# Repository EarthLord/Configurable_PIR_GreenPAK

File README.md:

# Project _PIR<sup>PAK</sup>_

### Objective

Create a PIR (Passive InfraRed) sensor system to detect movement using low cost AnalogPAK IC from Renesas (SLG47001). PIR sensors detect motion of heat, thus are used in security systems, building automation and wildlife conservation industries extensively. The sensitivity of sensing of movement is configurable by users using an `UP` and `DOWN` button.

### SLG47001 design 

### Schematic

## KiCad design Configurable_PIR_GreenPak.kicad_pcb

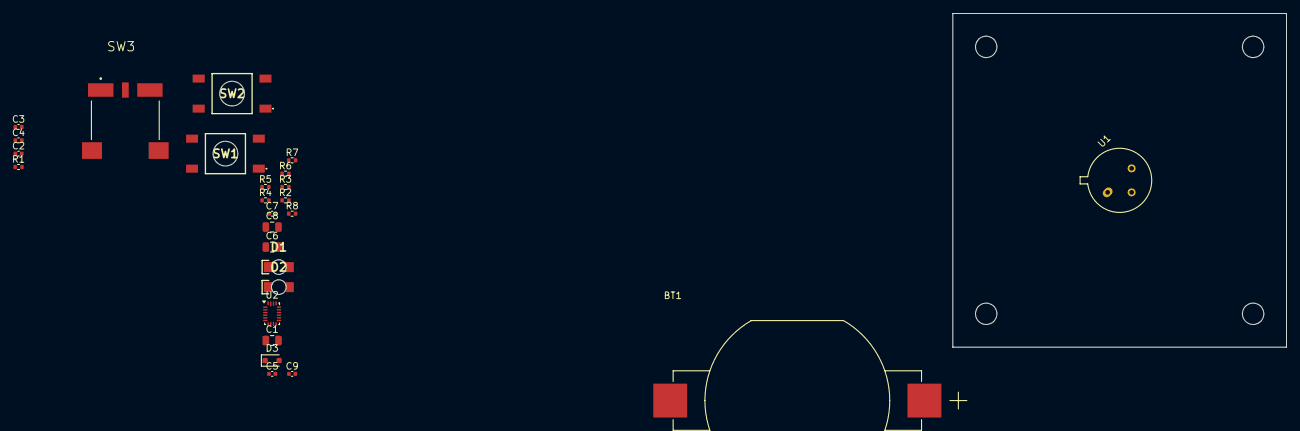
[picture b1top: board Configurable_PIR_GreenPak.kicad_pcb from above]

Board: 4 copper layers, 50.0 x 50.0 mm, 30 parts (0 on the bottom side), 18 nets, no tracks yet.

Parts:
BT1: Battery_Cell; MPD_BU2477SM-JJ-GTR
C1, C6, C8: 22u; C_0805_2012Metric
C2: 1n; C_0402_1005Metric
C3, C4, C5: 100n; C_0402_1005Metric
C7, C9: 6n8; C_0402_1005Metric
D1: Red LED; 5990Kxx_reverse_LED
D2: Green LED; 5990Kxx_reverse_LED
D3: CUS10S30,H3F; D_SOD-323
H1, H2, H3, H4: MountingHole; MountingHole_3.2mm_M3
R1, R4: 47k; R_0402_1005Metric
R2, R3: 510E; R_0402_1005Metric
R5, R6, R7, R8: 1M5; R_0402_1005Metric
SW1, SW2: SW_Push; RT3301AF100Q
SW3: SW_SPDT; SW_500ASSP1SM6QE
U1: PIR; TO-5-3
U2: SLG47001V; Renesas_UQFN-20_2x3mm_P0.4mm_LayoutBorder4x6y

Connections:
/DOWN_BTN: SW2.2, U2.15 (GPIO0)
/ENABLE_SW: SW3.2 (B), U2.1 (GPI0)
/LOW_BAT_LED: D1.1 (K), U2.19 (SDA/GPIO5)
/PIR_LED: D2.1 (K), U2.18 (SCL/GPIO4)
/PIR_OUT: C2.1, R1.1, U1.2 (OUT), U2.6 (OA0+)
/STAGE1_OUT: C7.2, C8.1, D3.2 (A), R5.2, U2.8 (OA0_OUT)
/STAGE2_OUT: C9.2, R6.2, U2.9 (OA1_OUT)
/UP_BTN: SW1.2, U2.16 (GPIO1)
/VBAT: BT1.P (+), C1.1, C3.1, C4.1, C5.1, R2.2, R3.2, R7.2, U1.1 (VDD), U2.2 (VDD), U2.14 (VDDA)
/VDD/2_REF: R7.1, R8.2, U2.11 (OA1+)
GND: BT1.N, C1.2, C2.2, C3.2, C4.2, C5.2, C6.2, R1.2, R8.1, SW1.1, SW2.1, SW3.3 (C), U1.3 (GND), U2.3 (GND)
unnamed: C6.1, R4.1
unnamed: D1.2 (A), R2.1
unnamed: D2.2 (A), R3.1
unnamed: C7.1, D3.1 (K), R4.2, R5.1, U2.7 (OA0-)
unnamed: U2.4 (RH0_A/GPI1), U2.12 (RH1_B/GPI3)
unnamed: C9.1, R6.1, U2.5 (RH0_B/GPI2), U2.10 (OA1-)
unnamed: C8.2, U2.13 (RH1_A/GPI4)

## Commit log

2025-09-01 Create initial commit of PIRPAK project
    Schematic finished with part numbers assigned to all parts except passives
    Basic readme created
2025-09-01 Correct title in README
2025-09-01 Add schematic pdf in schematic folder and show it in README
2025-09-01 Add 3D models of button, switch, LED, SLG47001V and cell holder
2025-09-01 Add footprints of all parts
2025-09-01 Create basic PCB layout after assigning footprints to all schematic symbols
